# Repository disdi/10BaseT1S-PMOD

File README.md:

# 10BASE-T1S PMOD

10BASE-T1S PMOD is a 3.3 V IEEE 802.3cg 10BASE-T1S transceiver module using a
Microchip LAN8670 in RMII. The host must provide the MAC. The first intended
host is an Arty A7-100T, plugged into JB.

The project is **KiCad 9.0.8**, revision **0.2**, dated 2026-10-26. Open
[kicad/step0.kicad_pro](kicad/step0.kicad_pro). The four-layer, 1.6 mm board is
70 × 20.32 mm with 2 mm corner radii and 48 footprints.

This revision uses an Arty JB direct-plug pinout: CLK50 on pin 1, TXD0 on
pin 10, with separate 33 Ω series resistors on the oscillator outputs to the
PHY and to the FPGA. ERC reports 0 errors and 93 expected open-stub warnings.
DRC with schematic parity reports 0 violations and 0 unconnected items.

## PMOD connections

**J1** is the 12-pin PMOD header for Arty A7 JB. This pinout is specific to
that host.

| PMOD pin | Signal | Function |
| --- | --- | --- |
| 1 | CLK50 | 50 MHz from this module to Arty E15/SRCC |
| 2 | TXD1 | RMII transmit data |
| 3 | TXEN | RMII transmit enable |
| 4 | CRS_DV | RMII carrier / data valid |
| 5 | GND | Ground |
| 6 | 3.3 V | Supply from host |
| 7 | RXD0 | RMII receive data |
| 8 | RXD1 | RMII receive data |
| 9 | RST_N | PHY reset, also pulled up on the module |
| 10 | TXD0 | RMII transmit data |
| 11 | GND | Ground |
| 12 | 3.3 V | Supply from host |

**J2** is the 5.00 mm-pitch cable terminal: pin 1 TRX_P, pin 2 TRX_N.
**J3** is the MDIO header: pin 1 MDC, pin 2 MDIO, pin 3 GND.
**JP1** and **JP2** enable the 100 Ω end-node termination when both shunts are
fitted. Leave both open for a drop node.

The PHY address is 0. PLCA node ID is a register, programmed over MDIO.
MODE[1:0] is 10 (RMII). The oscillator is a Kyocera KC2520Z 50 MHz part,
`KC2520Z50.0000C1KX00`. RBIAS is 12.4 kΩ 1%. The analog chain is PHY TRXP/TRXN,
0 Ω, TDK ACT1210D CMC, 100 nF 100 V, then J2. ESD parts are Panasonic
EZA-EG3W11AV.

## Files in this revision

| Path | Role |
| --- | --- |
| [LICENSE](LICENSE) | MIT, copyright 2024 disdi |
| [kicad/step0.kicad_pro](kicad/step0.kicad_pro) | KiCad 9 project |
| [kicad/step0.kicad_sch](kicad/step0.kicad_sch) | Schematic |
| [kicad/step0.kicad_pcb](kicad/step0.kicad_pcb) | Board |
| [kicad/fp-lib-table](kicad/fp-lib-table) | Local footprint table (`${KIPRJMOD}`) |
| [kicad/sym-lib-table](kicad/sym-lib-table) | Local symbol table (`${KIPRJMOD}`) |
| [kicad/libs/step0.kicad_sym](kicad/libs/step0.kicad_sym) | LAN8670 and PMOD symbols |
| [kicad/libs/pmod.kicad_sym](kicad/libs/pmod.kicad_sym) | Upstream PMOD symbols |
| [kicad/libs/pmod-conn_6x2.pretty/](kicad/libs/pmod-conn_6x2.pretty/) | PMOD 6×2 land |
| [kicad/libs/ACT1210.pretty/ACT1210D.kicad_mod](kicad/libs/ACT1210.pretty/ACT1210D.kicad_mod) | TDK ACT1210D land |
| [kicad/output_files/BOM-step0.csv](kicad/output_files/BOM-step0.csv) | BOM, 48 components |
| [kicad/output_files/CPL-step0.csv](kicad/output_files/CPL-step0.csv) | Pick-and-place |
| [kicad/output_files/gerbers/](kicad/output_files/gerbers/) | Gerbers and PTH/NPTH drill |

U2 clock qualification, Arty host timing and physical mating, stackup/DFM,
ferrite land acceptance, and assembler placement preview remain open. Clean
ERC/DRC is not fabrication approval.

License: [MIT, copyright 2024 disdi](LICENSE).
The [PMOD library notice](kicad/libs/pmod-LICENSE) accompanies that library.

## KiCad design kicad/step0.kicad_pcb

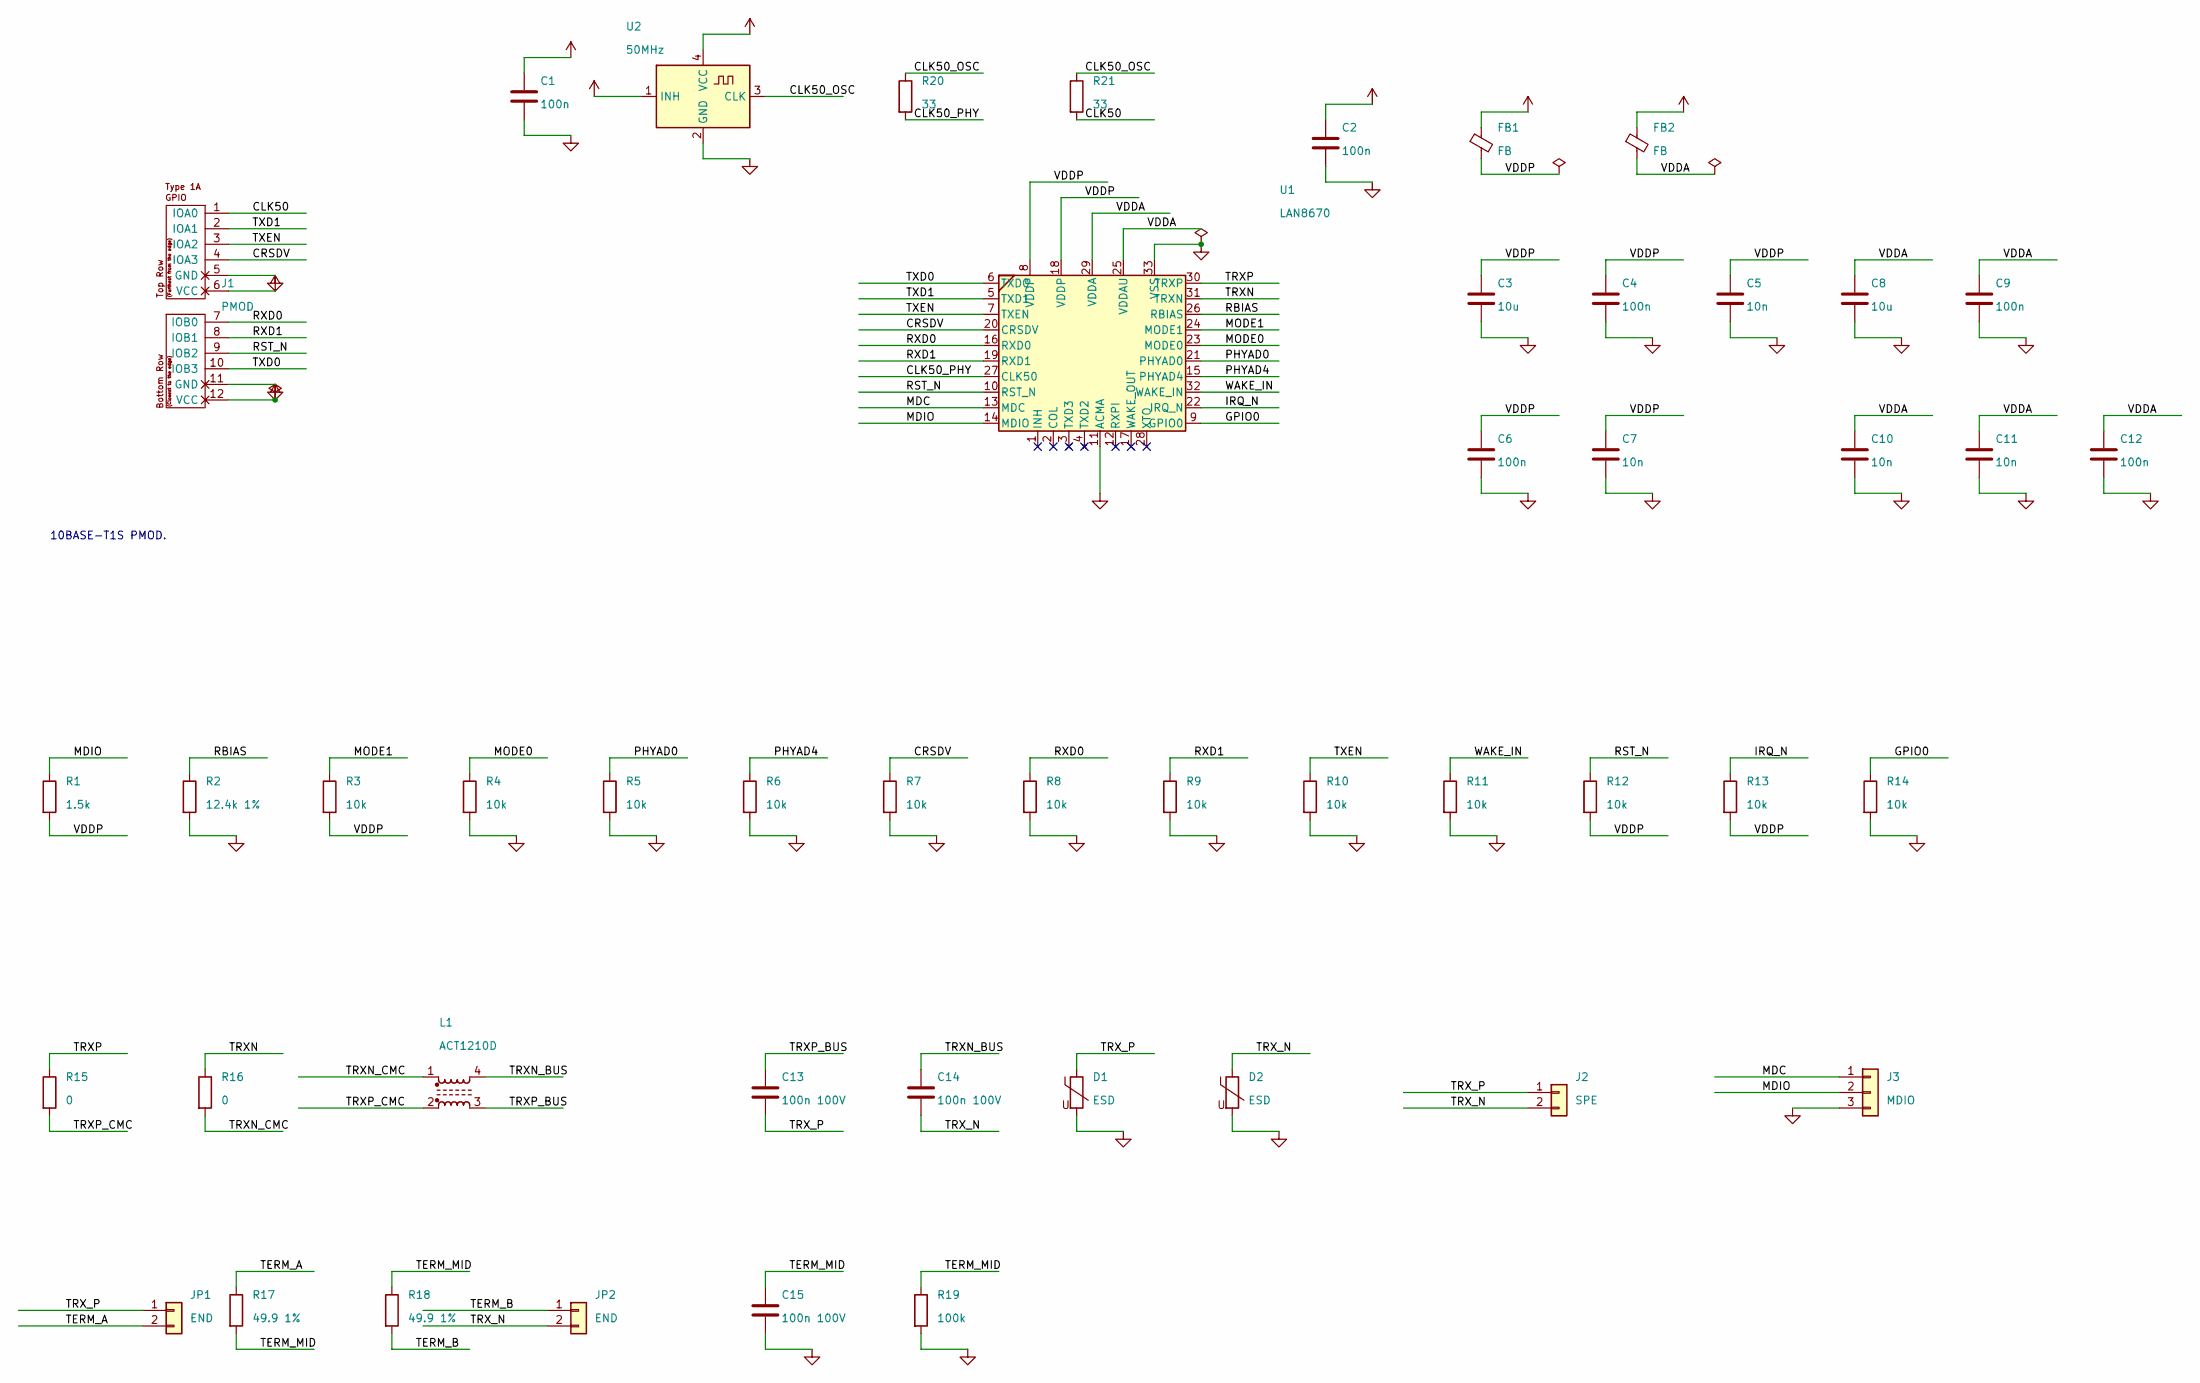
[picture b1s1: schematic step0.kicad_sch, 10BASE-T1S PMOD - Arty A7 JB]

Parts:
C1, C2, C4, C6, C9, C12: 100n; C_0402_1005Metric
C3, C8: 10u; C_0805_2012Metric
C5, C7, C10, C11: 10n; C_0402_1005Metric
C13, C14, C15: 100n 100V; C_0805_2012Metric; MPN 885012207128
D1, D2: ESD; D_0603_1608Metric; MPN EZA-EG3W11AV
FB1, FB2: FB; R_0805_2012Metric; MPN 742792640
J1: PMOD; pmod_pin_array_6x2
J2: SPE; TerminalBlock_Phoenix_MKDS-1,5-2_1x02_P5.00mm_Horizontal; MPN 691102710002
J3: MDIO; PinHeader_1x03_P2.54mm_Vertical
JP1, JP2: END; PinHeader_1x02_P2.00mm_Vertical; MPN 62000211121
L1: ACT1210D; MPN ACT1210D-131-2P-TL00
R1: 1.5k; R_0402_1005Metric
R2: 12.4k 1%; R_0603_1608Metric; MPN ERJP03F1242V
R3, R4, R5, R6, R7, R8, R9, R10, R11, R12, R13, R14: 10k; R_0402_1005Metric
R15, R16: 0; R_0402_1005Metric; MPN ERJ-2GE0R00X
R17, R18: 49.9 1%; R_0603_1608Metric; MPN ERJP03F49R9V
R19: 100k; R_0603_1608Metric
R20, R21: 33; R_0402_1005Metric
U1: LAN8670; QFN-32-1EP_5x5mm_P0.5mm_EP3.45x3.45mm; MPN LAN8670C2T-E/LMX
U2: 50MHz; Oscillator_SMD_Kyocera_KC2520Z-4Pin_2.5x2.0mm; MPN KC2520Z50.0000C1KX00

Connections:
+3V3: C1.1, C2.1, FB1.1, FB2.1, J1.6 (VCC), J1.12 (VCC), U2.1 (INH), U2.4 (VCC)
/CLK50: J1.1 (IOA0), R21.2
/CLK50_OSC: R20.1, R21.1, U2.3 (CLK)
/CLK50_PHY: R20.2, U1.27 (CLK50)
/CRSDV: J1.4 (IOA3), R7.1, U1.20 (CRSDV)
/GPIO0: R14.1, U1.9 (GPIO0)
/IRQ_N: R13.1, U1.22 (IRQ_N)
/MDC: J3.1, U1.13 (MDC)
/MDIO: J3.2, R1.1, U1.14 (MDIO)
/MODE0: R4.1, U1.23 (MODE0)
/MODE1: R3.1, U1.24 (MODE1)
/PHYAD0: R5.1, U1.21 (PHYAD0)
/PHYAD4: R6.1, U1.15 (PHYAD4)
/RBIAS: R2.1, U1.26 (RBIAS)
/RST_N: J1.9 (IOB2), R12.1, U1.10 (RST_N)
/RXD0: J1.7 (IOB0), R8.1, U1.16 (RXD0)
/RXD1: J1.8 (IOB1), R9.1, U1.19 (RXD1)
/TERM_A: JP1.2, R17.1
/TERM_B: JP2.1, R18.2
/TERM_MID: C15.1, R17.2, R18.1, R19.1
/TRXN: R16.1, U1.31 (TRXN)
/TRXN_BUS: C14.1, L1.4
/TRXN_CMC: L1.1, R16.2
/TRXP: R15.1, U1.30 (TRXP)
/TRXP_BUS: C13.1, L1.3
/TRXP_CMC: L1.2, R15.2
/TRX_N: C14.2, D2.1, J2.2, JP2.2
/TRX_P: C13.2, D1.1, J2.1, JP1.1
/TXD0: J1.10 (IOB3), U1.6 (TXD0)
/TXD1: J1.2 (IOA1), U1.5 (TXD1)
/TXEN: J1.3 (IOA2), R10.1, U1.7 (TXEN)
/WAKE_IN: R11.1, U1.32 (WAKE_IN)
GND: C1.2, C2.2, C3.2, C4.2, C5.2, C6.2, C7.2, C8.2, C9.2, C10.2, C11.2, C12.2, C15.2, D1.2, D2.2, J1.5 (GND), J1.11 (GND), J3.3, R2.2, R4.2, R5.2, R6.2, R7.2, R8.2, R9.2, R10.2, R11.2, R14.2, R19.2, U1.11 (ACMA), U1.33 (VSS), U2.2 (GND)

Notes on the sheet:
10BASE-T1S PMOD.

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
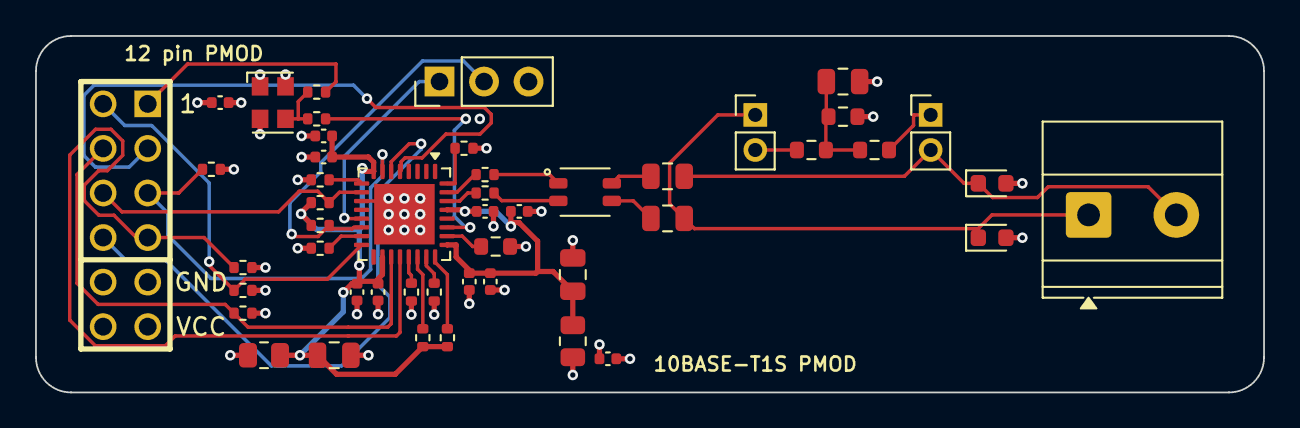
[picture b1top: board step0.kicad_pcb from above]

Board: 4 copper layers, 70.0 x 20.3 mm, 48 parts (0 on the bottom side), 35 nets.

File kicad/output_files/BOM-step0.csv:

"References","Value","MPN","Manufacturer","Footprint","Description","Quantity","DNP"
"C1","100n","","","Capacitor_SMD:C_0402_1005Metric","Oscillator local decoupling, 100 nF, 0402.","1",""
"C2","100n","","","Capacitor_SMD:C_0402_1005Metric","+3V3 decoupling at the PMOD, 100 nF, 0402.","1",""
"C3","10u","","","Capacitor_SMD:C_0805_2012Metric","VDDP bulk, 10 µF, 0805, X5R. Device side of FB1.","1",""
"C4","100n","","","Capacitor_SMD:C_0402_1005Metric","VDDP pin 8, 100 nF, 0402.","1",""
"C5","10n","","","Capacitor_SMD:C_0402_1005Metric","VDDP pin 8, 10 nF, closest to the pin, 0402.","1",""
"C6","100n","","","Capacitor_SMD:C_0402_1005Metric","VDDP pin 18, 100 nF, 0402.","1",""
"C7","10n","","","Capacitor_SMD:C_0402_1005Metric","VDDP pin 18, 10 nF, closest to the pin, 0402.","1",""
"C8","10u","","","Capacitor_SMD:C_0805_2012Metric","VDDA bulk, 10 µF, 0805, X5R. Device side of FB2.","1",""
"C9","100n","","","Capacitor_SMD:C_0402_1005Metric","VDDA pin 29, 100 nF, 0402.","1",""
"C10","10n","","","Capacitor_SMD:C_0402_1005Metric","VDDA pin 29, 10 nF, closest to the pin, 0402.","1",""
"C11","10n","","","Capacitor_SMD:C_0402_1005Metric","VDDAU pin 25, 10 nF, 0402. VDDAU is tied to VDDA.","1",""
"C12","100n","","","Capacitor_SMD:C_0402_1005Metric","VDDAU pin 25, 100 nF, 0402.","1",""
"C13","100n 100V","885012207128","","Capacitor_SMD:C_0805_2012Metric","Cable-side coupling, 100 nF, 100 V, 0805, on TRXP.","1",""
"C14","100n 100V","885012207128","","Capacitor_SMD:C_0805_2012Metric","Cable-side coupling, 100 nF, 100 V, 0805, on TRXN.","1",""
"C15","100n 100V","885012207128","","Capacitor_SMD:C_0805_2012Metric","Termination common-mode capacitor, 100 nF, 100 V, 0805.","1",""
"D1","ESD","EZA-EG3W11AV","","Diode_SMD:D_0603_1608Metric","Bidirectional ESD suppressor, TRX_P to GND.","1",""
"D2","ESD","EZA-EG3W11AV","","Diode_SMD:D_0603_1608Metric","Bidirectional ESD suppressor, TRX_N to GND.","1",""
"FB1","FB","742792640","","Resistor_SMD:R_0805_2012Metric","VDDP ferrite, 300 ohm at 100 MHz.","1",""
"FB2","FB","742792640","","Resistor_SMD:R_0805_2012Metric","VDDA and VDDAU ferrite, 300 ohm at 100 MHz.","1",""
"J1","PMOD","","","pmod-conn_6x2:pmod_pin_array_6x2","Arty A7 JB pinout: pin 1 CLK50 output, pin 10 TXD0 input. NOT Katze/LiteX pin compatible.","1",""
"J2","SPE","691102710002","","TerminalBlock_Phoenix:TerminalBlock_Phoenix_MKDS-1,5-2_1x02_P5.00mm_Horizontal","2-pin 5.00 mm screw terminal. Pin 1 TRX_P, pin 2 TRX_N.","1",""
"J3","MDIO","","","Connector_PinHeader_2.54mm:PinHeader_1x03_P2.54mm_Vertical","MDIO header. Pin 1 MDC, pin 2 MDIO, pin 3 GND. Required for PLCA.","1",""
"JP1","END","62000211121","","Connector_PinHeader_2.00mm:PinHeader_1x02_P2.00mm_Vertical","Fit both JP1 and JP2 for an end-node 100 ohm termination. Leave both open for a drop node.","1",""
"JP2","END","62000211121","","Connector_PinHeader_2.00mm:PinHeader_1x02_P2.00mm_Vertical","Fit both JP1 and JP2 for an end-node 100 ohm termination. Leave both open for a drop node.","1",""
"L1","ACT1210D","ACT1210D-131-2P-TL00","","ACT1210:ACT1210D","Common-mode choke. Windings 1-4 (TRXN) and 2-3 (TRXP). No polarity.","1",""
"R1","1.5k","","","Resistor_SMD:R_0402_1005Metric","MDIO pull-up, 1.5 kΩ to VDDP.","1",""
"R2","12.4k 1%","ERJP03F1242V","","Resistor_SMD:R_0603_1608Metric","RBIAS, 12.4 kΩ 1% to GND.","1",""
"R3","10k","","","Resistor_SMD:R_0402_1005Metric","MODE1 pull-up. RMII is MODE[1:0]=10.","1",""
"R4","10k","","","Resistor_SMD:R_0402_1005Metric","MODE0 pull-down. RMII is MODE[1:0]=10.","1",""
"R5","10k","","","Resistor_SMD:R_0402_1005Metric","PHYAD0 pull-down. Address bit 0, pin 21 RXER.","1",""
"R6","10k","","","Resistor_SMD:R_0402_1005Metric","PHYAD4 pull-down. Address bit 4, pin 15 CRS.","1",""
"R7","10k","","","Resistor_SMD:R_0402_1005Metric","PHYAD1 pull-down on CRSDV. Address bit 1.","1",""
"R8","10k","","","Resistor_SMD:R_0402_1005Metric","PHYAD2 pull-down on RXD0. Address bit 2.","1",""
"R9","10k","","","Resistor_SMD:R_0402_1005Metric","PHYAD3 pull-down on RXD1. Address bit 3.","1",""
"R10","10k","","","Resistor_SMD:R_0402_1005Metric","TXEN pull-down. Required while the MAC pin is Hi-Z.","1",""
"R11","10k","","","Resistor_SMD:R_0402_1005Metric","WAKE_IN pull-down, pin 32.","1",""
"R12","10k","","","Resistor_SMD:R_0402_1005Metric","RESET_N pull-up to VDDP. PMOD pin 9 also drives it.","1",""
"R13","10k","","","Resistor_SMD:R_0402_1005Metric","IRQ_N pull-up to VDDP. Not brought to the PMOD.","1",""
"R14","10k","","","Resistor_SMD:R_0402_1005Metric","GPIO0 pull-down.","1",""
"R15","0","ERJ-2GE0R00X","","Resistor_SMD:R_0402_1005Metric","Series 0 ohm on TRXP, PHY side of the CMC.","1",""
"R16","0","ERJ-2GE0R00X","","Resistor_SMD:R_0402_1005Metric","Series 0 ohm on TRXN, PHY side of the CMC.","1",""
"R17","49.9 1%","ERJP03F49R9V","","Resistor_SMD:R_0603_1608Metric","End-node termination, 49.9 Ω 1%.","1",""
"R18","49.9 1%","ERJP03F49R9V","","Resistor_SMD:R_0603_1608Metric","End-node termination, 49.9 Ω 1%.","1",""
"R19","100k","","","Resistor_SMD:R_0603_1608Metric","Termination bleed, 100 kΩ to GND.","1",""
"R20","33","","","Resistor_SMD:R_0402_1005Metric","33 ohm clock source termination; tune by signal-integrity measurement.","1",""
"R21","33","","","Resistor_SMD:R_0402_1005Metric","33 ohm clock source termination; tune by signal-integrity measurement.","1",""
"U1","LAN8670","LAN8670C2T-E/LMX","","Package_DFN_QFN:QFN-32-1EP_5x5mm_P0.5mm_EP3.45x3.45mm","LAN8670 RMII. MODE[1:0]=10. PHY address 0. Exposed pad is pin 33, VSS.","1",""
"U2","50MHz","KC2520Z50.0000C1KX00","KYOCERA AVX","Oscillator:Oscillator_SMD_Kyocera_KC2520Z-4Pin_2.5x2.0mm","KYOCERA AVX KC2520Z50.0000C1KX00. 3.3 V, 50 MHz, ±20 ppm, -40 to +85 C. Output enable (pin 1) tied high. Drives REFCLKIN and Arty JB pin 1 through separate 33 ohm resistors.","1",""
